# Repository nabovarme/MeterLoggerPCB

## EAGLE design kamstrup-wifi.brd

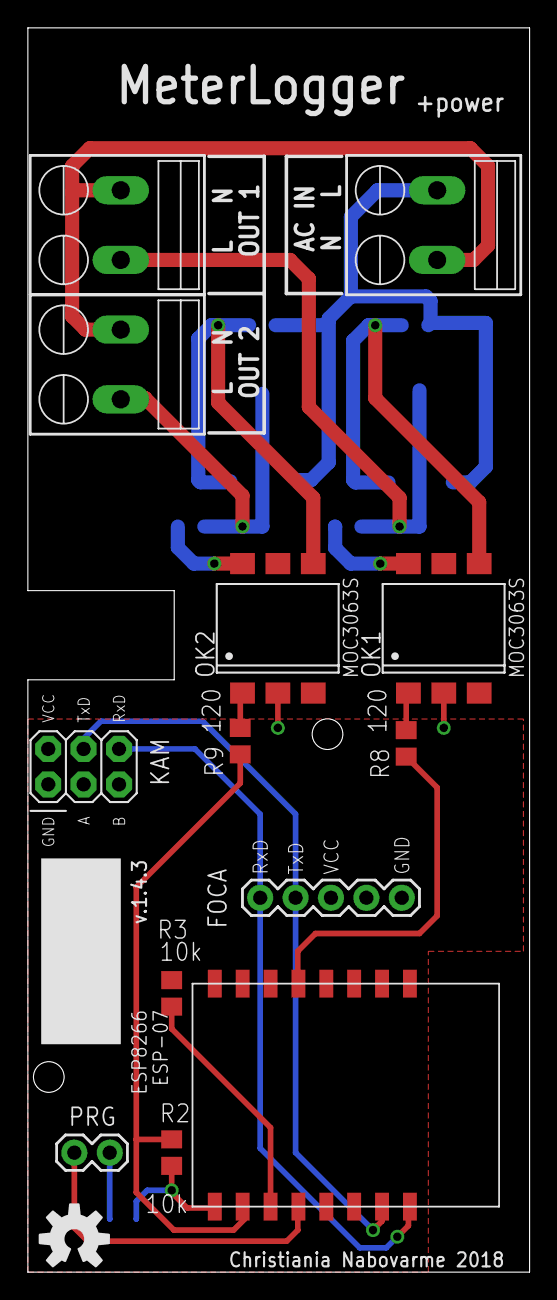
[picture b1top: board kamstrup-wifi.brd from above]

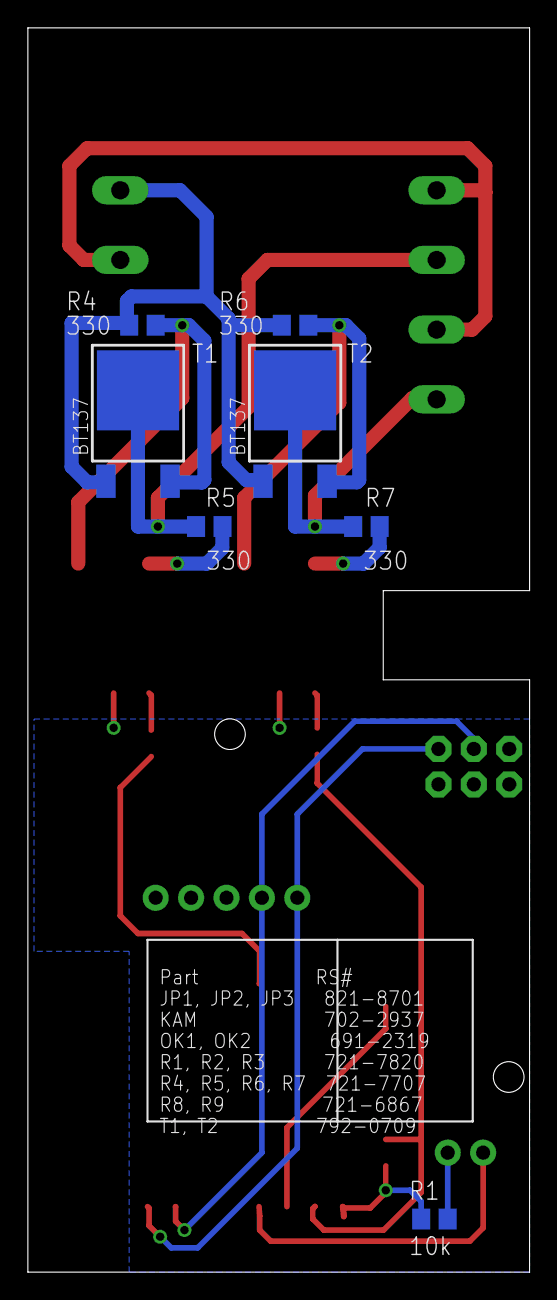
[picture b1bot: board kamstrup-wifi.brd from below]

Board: 2 copper layers, 36.0 x 89.3 mm, 21 parts (7 on the bottom side), 19 nets.

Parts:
FOCA: 1X05
JP1: AC IN; SCREWTERMINAL-5MM-2
JP2: AC OUT 1; SCREWTERMINAL-5MM-2
JP3: AC OUT 2; SCREWTERMINAL-5MM-2
KAM: 2X03
OK1, OK2: MOC3063S; DIL6-SMD
PRG: M02PTH; 1X02
R1, R2, R3: 10k; R0805
R4, R5, R6, R7: 330; R0805
R8, R9: 120; R0805
T1, T2: BT137; SOT428
U1: ESP8266-07; ESP-07
U$2: OSHW-LOGO-M

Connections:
3.3V: FOCA.3, KAM.2, R3.1, U1.CH_PD, U1.VCC
GND: FOCA.5, KAM.1, OK1.2, OK2.2, R1.1, R2.1, U1.GND
unnamed: FOCA.1, KAM.6, U1.TXD
unnamed: FOCA.2, KAM.4, U1.RXD
unnamed: PRG.2, U1.GPIO0
unnamed: PRG.1, R1.2
unnamed: OK2.1, R9.2
unnamed: OK2.4, R6.1, T2.3
unnamed: OK2.6, R7.1
unnamed: JP3.1, R7.2, T2.4
unnamed: JP1.2, R4.2, R6.2, T1.1, T2.1
unnamed: R8.1, U1.GPIO14
unnamed: OK1.1, R8.2
unnamed: OK1.4, R4.1, T1.3
unnamed: OK1.6, R5.1
unnamed: JP2.1, R5.2, T1.4
unnamed: R2.2, R9.1, U1.GPIO15
unnamed: JP1.1, JP2.2, JP3.2
unnamed: R3.2, U1.GPIO2

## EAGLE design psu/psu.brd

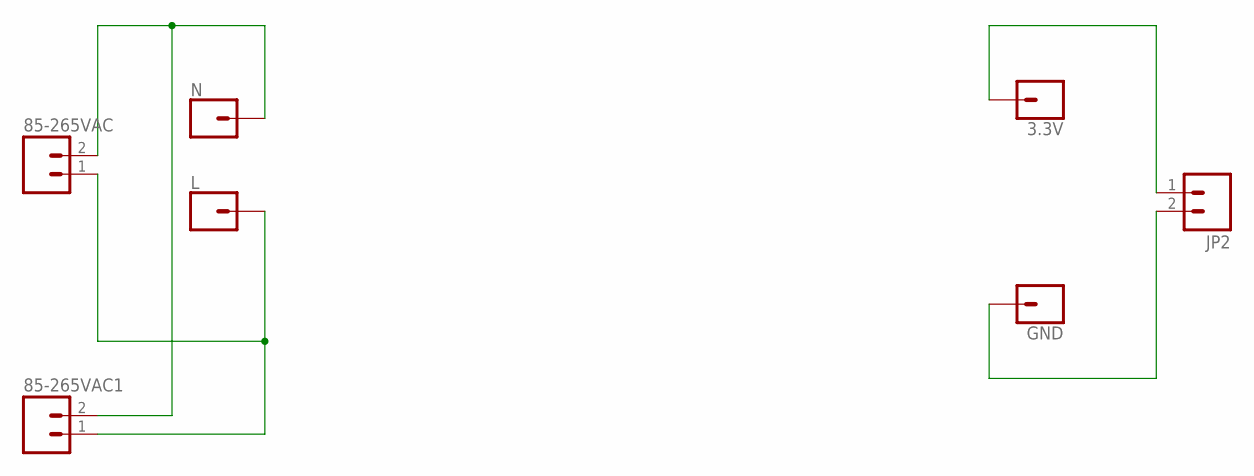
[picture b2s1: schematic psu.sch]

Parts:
3.3V: CONN_01PTH_1.4MM; 1X01_1.4MM
85-265VAC, 85-265VAC1: M02PTH3_5MM; 1X02_LONGPADS
GND: CONN_01PTH_1.4MM; 1X01_1.4MM
JP2: M02PTH3_5MM; 1X02_LONGPADS
L: CONN_01PTH_1.4MM; 1X01_1.4MM
N: CONN_01PTH_1.4MM; 1X01_1.4MM

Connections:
unnamed: 85-265VAC.1, 85-265VAC1.1, L.1
unnamed: 85-265VAC.2, 85-265VAC1.2, N.1
unnamed: 3.3V.1, JP2.1
unnamed: GND.1, JP2.2

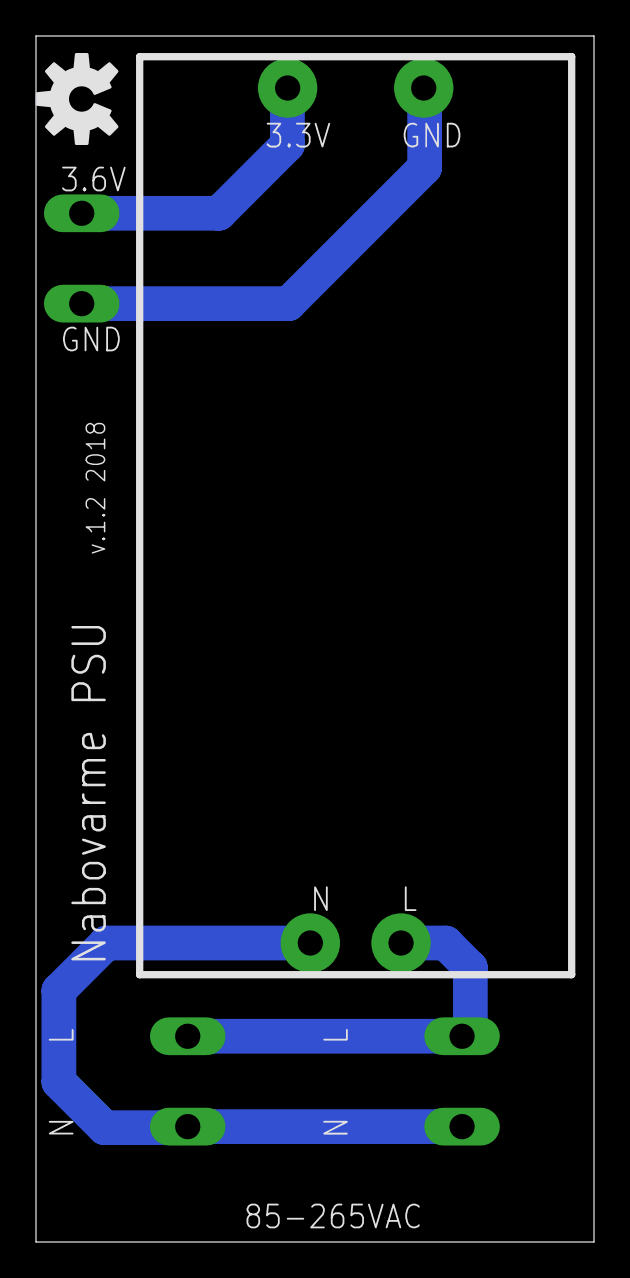
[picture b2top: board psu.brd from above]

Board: 2 copper layers, 31.0 x 67.0 mm, 8 parts (0 on the bottom side), 4 nets.

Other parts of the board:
U$1: OSHW-LOGO-M

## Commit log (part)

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2015-09-15 added pcb+power from f81b98b96438f6aeb28dbc087c39275dec301eaf
2016-05-18 v.1.2.1
    + watchdog and pulldown on gpio 15
2016-05-29 PCB: v.1.4.1 Added FeRAM
    + docs
2016-11-19 added pull up resistor on GPIO02
2017-04-21 added missing pull down (R12) on pcb
2017-04-23 reverted pcb to v 1.2.1 2377baf1af9bc101ab4e1265beb616f56084d54c no pull down needed
2017-10-08 Labels for N and L on AC in/out
2017-10-09 pcb board made 8 mm higher for better fixation in kamstrup meter
2017-10-17 updated pdf's
    for schematics and pcb
2017-10-17 moved meterlogger_doxygen to submodule
2017-10-17 moved pcb/psu to pcb+power/psu
2017-10-19 RS # for R4, R5, R8, R9 changed
2017-10-23 Missing R11 value fixed
2017-10-23 version bumbed to 1.2.5
2017-10-25 rotated jp1, jp3 and jp3
2017-10-25 removed snubber circuits and external watchdog timer ic now version 1.3.0
2017-10-25 changed some via size v 1.3.1
2017-10-25 updated pdfs from latest version (v.1.3.1)
2018-04-27 updated psi pcb
    3.3V -> 3.6V
    v.1.1 -> v.1.2
    2015 -> 2018
2018-04-28 psu pcb: smaller holes for psu module
2018-04-28 psi pcb: better silk layout
2018-05-09 programmer connector moved
2018-05-11 Sdcard
2018-05-11 Silk updated
2018-05-11 Version sent to pcb fabrication

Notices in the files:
parts and their libraries:
SparkFun-Connectors: Licensing: CC v3.0 Share-Alike You are welcome to use this library for commercial purposes.
1X01: Licensing: Creative Commons ShareAlike 4.0 International - https://creativecommons.org/licenses/by-sa/4.0
